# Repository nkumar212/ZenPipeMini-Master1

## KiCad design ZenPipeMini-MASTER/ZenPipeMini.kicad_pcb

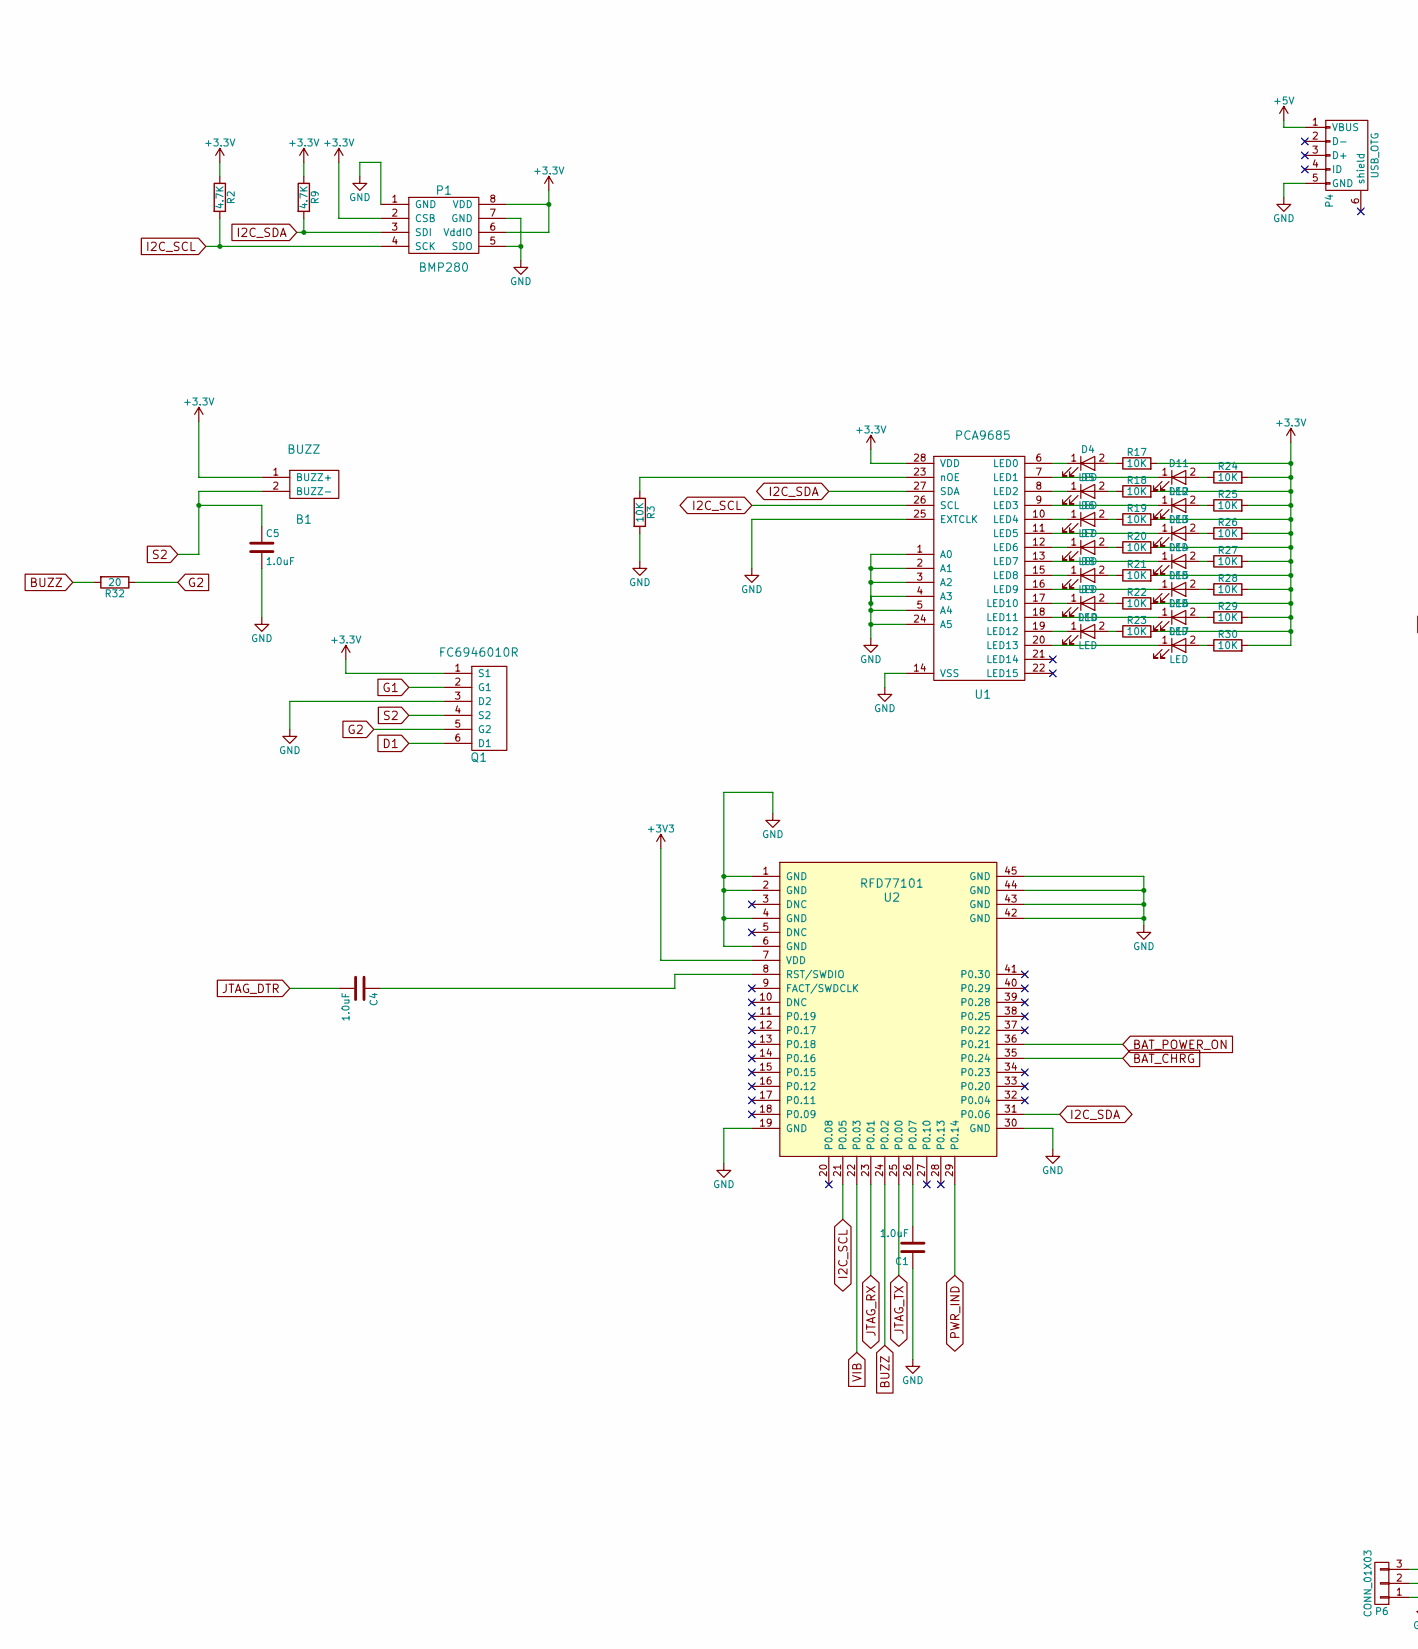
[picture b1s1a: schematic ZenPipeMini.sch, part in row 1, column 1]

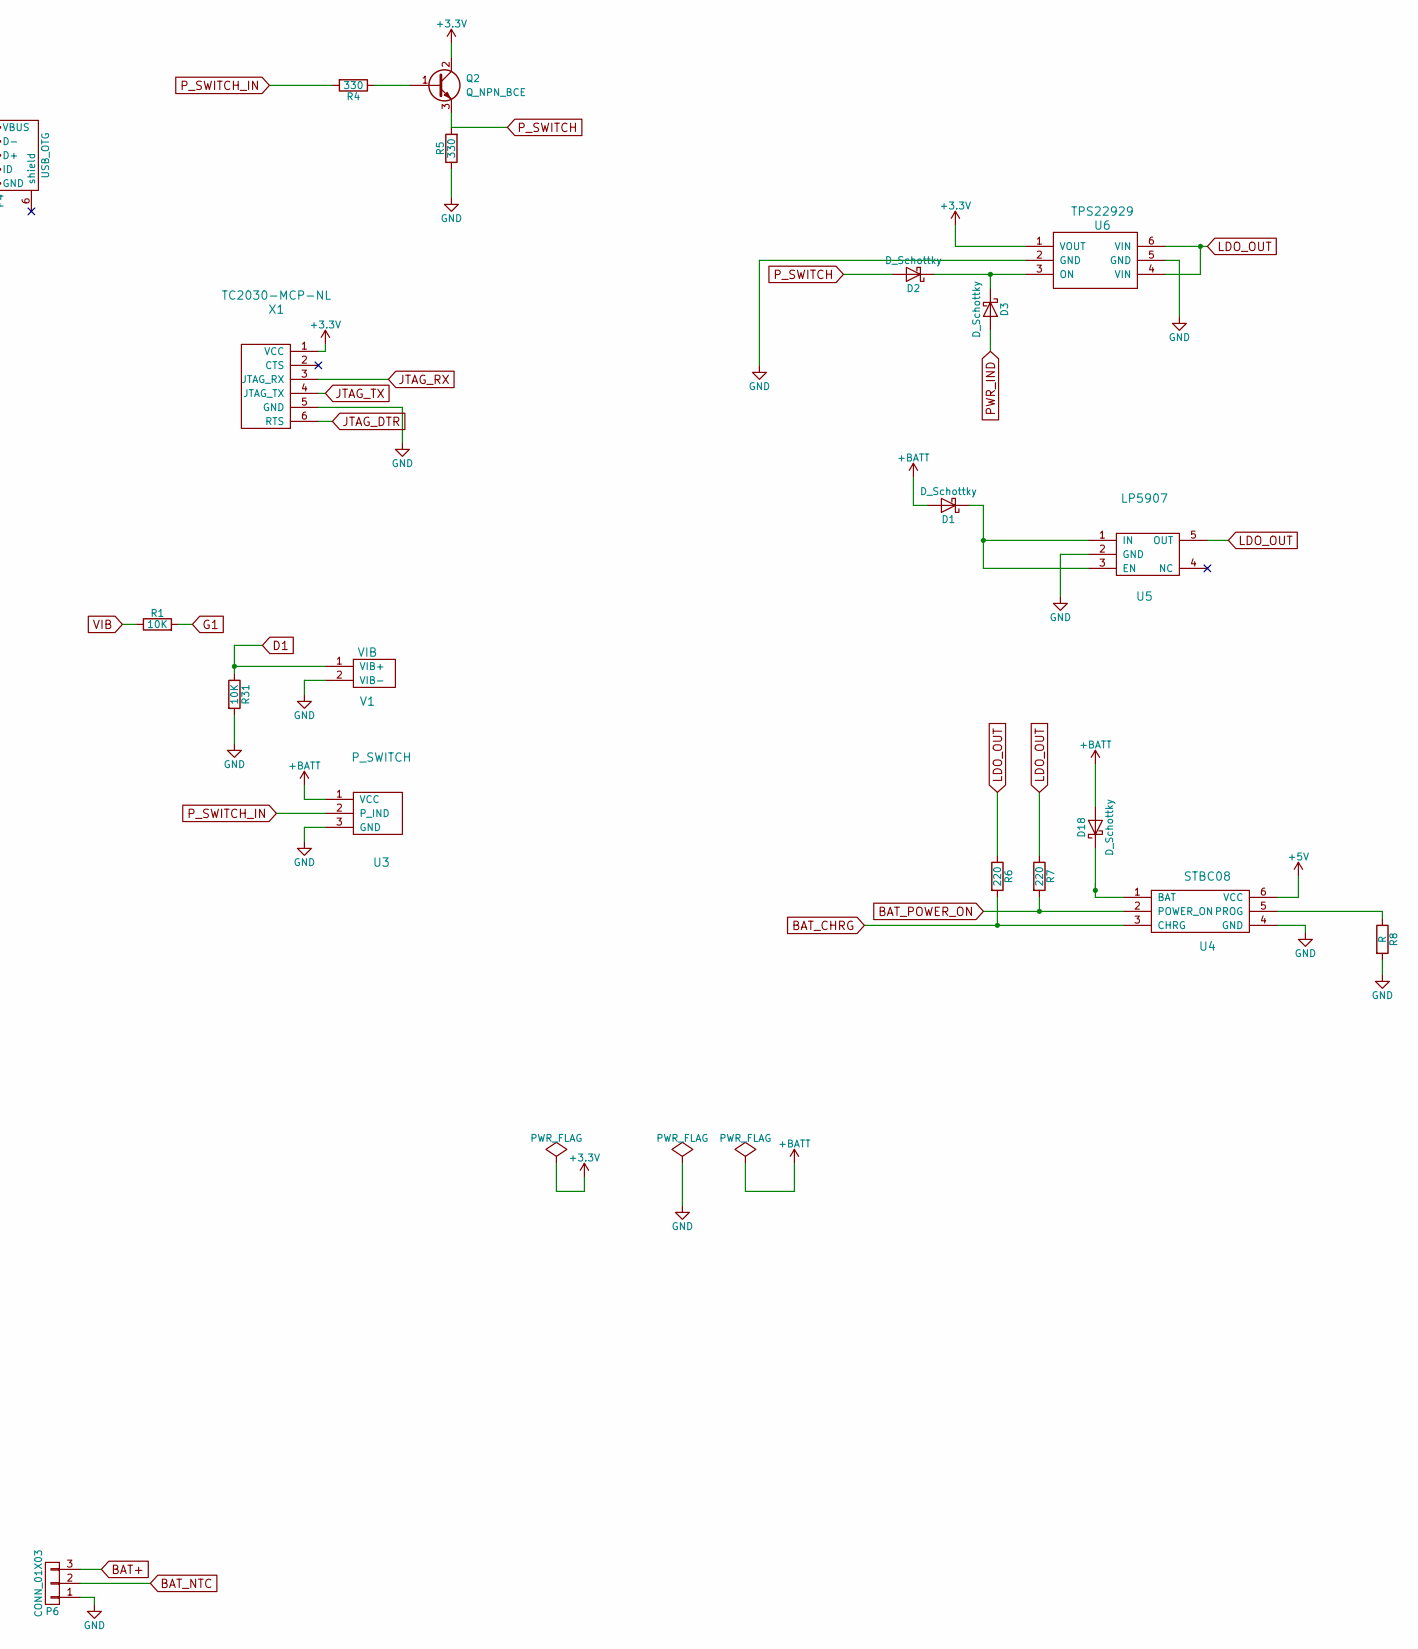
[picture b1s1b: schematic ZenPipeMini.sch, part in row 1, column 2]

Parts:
B1: BUZZ
C1, C4, C5: 1.0uF; C_0201
D1, D2, D3, D18: D_Schottky; D_0603
D4, D5, D6, D7, D8, D9, D10, D11, D12, D13, D14, D15, D16, D17: LED; LED_0402
P1: BMP280
P4: USB_OTG; USB_Micro-B
P6: CONN_01X03; BAT
Q1: FC6946010R
Q2: Q_NPN_BCE; SOT-23
R1, R3, R17, R18, R19, R20, R21, R22, R23, R24, R25, R26, R27, R28, R29, R30, R31: 10K; R_0201
R2, R9: 4.7K; R_0201
R4, R5: 330; R_0201
R6, R7: 220; R_0201
R8: R; R_0201
R32: 20; R_0201
U1: PCA9685; PCA9685_QFN
U2: RFD77101
U3: P_SWITCH
U4: STBC08
U5: LP5907
U6: TPS22929
V1: VIB
X1: TC2030-MCP-NL

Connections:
+5V: P4.1 (VBUS), U4.6 (VCC)
+BATT: D1.2 (A), D18.2 (A), U3.1 (VCC)
BAT+: P6.3
BAT_CHRG: R6.2, U2.35 (P0.24), U4.3 (CHRG)
BAT_NTC: P6.2
BAT_POWER_ON: R7.2, U2.36 (P0.21), U4.2 (POWER_ON)
BUZZ: R32.2, U2.24 (P0.02)
D1: Q1.6 (D1), R31.1, V1.1 (VIB+)
G1: Q1.2 (G1), R1.2
G2: Q1.5 (G2), R32.1
GND: C1.1, C5.2, P1.1 (GND), P1.5 (SDO), P1.7 (GND), P4.5 (GND), P6.1, Q1.3 (D2), R3.2, R5.1, R8.2, R31.2, U1.1 (A0), U1.2 (A1), U1.3 (A2), U1.4 (A3), U1.5 (A4), U1.14 (VSS), U1.24 (A5), U1.25 (EXTCLK), U2.1 (GND), U2.2 (GND), U2.4 (GND), U2.6 (GND), U2.19 (GND), U2.30 (GND), U2.42 (GND), U2.43 (GND), U2.44 (GND), U2.45 (GND), U3.3 (GND), U4.4 (GND), U5.2 (GND), U6.2 (GND), U6.5 (GND), V1.2 (VIB-), X1.5 (GND)
I2C_SCL: P1.4 (SCK), R2.2, U1.26 (SCL), U2.21 (P0.05)
I2C_SDA: P1.3 (SDI), R9.2, U1.27 (SDA), U2.31 (P0.06)
JTAG_DTR: C4.2, X1.6 (RTS)
JTAG_RX: U2.23 (P0.01), X1.3 (JTAG_RX)
JTAG_TX: U2.25 (P0.00), X1.4 (JTAG_TX)
LDO_OUT: R6.1, R7.1, U5.5 (OUT), U6.4 (VIN), U6.6 (VIN)
unnamed: C1.2, U2.26 (P0.07)
unnamed: C4.1, U2.8 (RST/SWDIO)
unnamed: D1.1 (K), U5.1 (IN), U5.3 (EN)
unnamed: D2.1 (K), D3.1 (K), U6.3 (ON)
unnamed: D4.1 (K), U1.6 (LED0)
unnamed: D4.2 (A), R17.1
unnamed: D5.1 (K), U1.8 (LED2)
unnamed: D5.2 (A), R18.1
unnamed: D6.1 (K), U1.10 (LED4)
unnamed: D6.2 (A), R19.1
unnamed: D7.1 (K), U1.12 (LED6)
unnamed: D7.2 (A), R20.1
unnamed: D8.1 (K), U1.15 (LED8)
unnamed: D8.2 (A), R21.1
unnamed: D9.1 (K), U1.17 (LED10)
unnamed: D9.2 (A), R22.1
unnamed: D10.1 (K), U1.19 (LED12)
unnamed: D10.2 (A), R23.1
unnamed: D11.1 (K), U1.7 (LED1)
unnamed: D11.2 (A), R24.1
unnamed: D12.1 (K), U1.9 (LED3)
unnamed: D12.2 (A), R25.1
unnamed: D13.1 (K), U1.11 (LED5)
unnamed: D13.2 (A), R26.1
unnamed: D14.1 (K), U1.13 (LED7)
unnamed: D14.2 (A), R27.1
unnamed: D15.1 (K), U1.16 (LED9)
unnamed: D15.2 (A), R28.1
unnamed: D16.1 (K), U1.18 (LED11)
unnamed: D16.2 (A), R29.1
unnamed: D17.1 (K), U1.20 (LED13)
unnamed: D17.2 (A), R30.1
unnamed: D18.1 (K), U4.1 (BAT)
unnamed: Q2.1 (B), R4.1
unnamed: R3.1, U1.23 (nOE)
unnamed: R8.1, U4.5 (PROG)
PWR_IND: D3.2 (A), U2.29 (P0.14)
P_SWITCH: D2.2 (A), Q2.3 (E), R5.2
P_SWITCH_IN: R4.2, U3.2 (P_IND)
S2: B1.2 (BUZZ-), C5.1, Q1.4 (S2)
VIB: R1.1, U2.22 (P0.03)

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
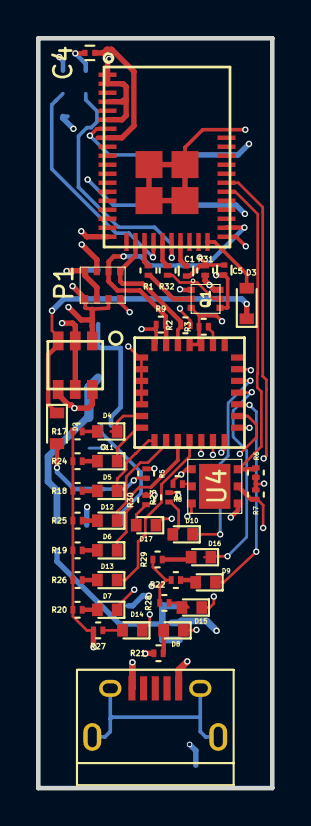
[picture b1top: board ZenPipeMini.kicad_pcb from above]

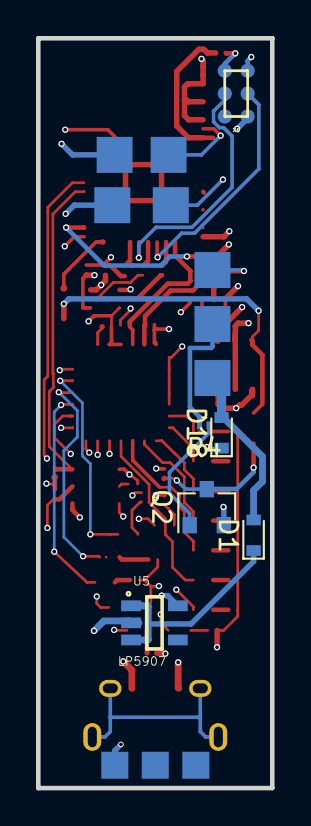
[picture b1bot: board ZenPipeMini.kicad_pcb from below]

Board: 4 copper layers, 13.0 x 41.7 mm, 60 parts (10 on the bottom side), 57 nets.

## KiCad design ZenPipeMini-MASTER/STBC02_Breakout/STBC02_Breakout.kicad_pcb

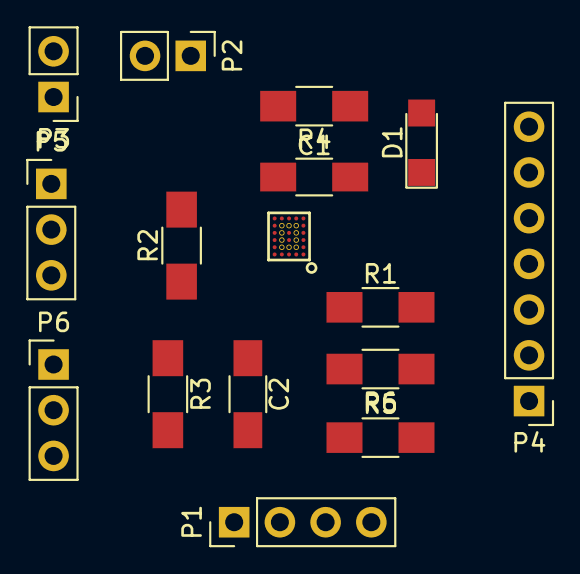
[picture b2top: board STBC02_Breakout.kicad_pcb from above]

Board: 2 copper layers, 16 parts (0 on the bottom side), 25 nets, no tracks yet.

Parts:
C1, C2: C; C_1206_HandSoldering
D1: LED; LED_1206
P1: CONN_01X04; Pin_Header_Straight_1x04_Pitch2.54mm
P2, P3: CONN_01X02; Pin_Header_Straight_1x02_Pitch2.54mm
P4: CONN_01X07; Pin_Header_Straight_1x07_Pitch2.54mm
P5, P6: CONN_01X03; Pin_Header_Straight_1x03_Pitch2.54mm
R1, R2, R3, R4, R5, R6: R; R_1206_HandSoldering
U1: STBC02

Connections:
+5V: U1.E5, U1.F5
BAT+: C2.1, P1.1, R3.1, U1.A5, U1.B3, U1.B5
BATMS: P1.2, R5.1, R6.2
BAT_NTC: P1.3, U1.D1
CEN: P4.2, U1.B1
GND: C2.2, P1.4, P2.2, P3.2, R1.2, R2.2, R6.1, U1.A3, U1.B4
LDO: C1.1, P2.1, R4.2, U1.F4
unnamed: D1.2, R4.1
unnamed: R1.1, U1.A4
unnamed: R2.1, U1.D4
unnamed: R3.2, U1.A2
unnamed: R5.2, U1.C4
RESET_NOW: P4.3, U1.A1
RST_PENDING: P4.4, U1.B2
SW1_I: P6.1, U1.F3
SW1_OA: P6.2, U1.E4
SW1_OB: P6.3, U1.E3
SW2_I: P5.1, U1.E2
SW2_OA: P5.2, U1.F2
SW2_OB: P5.3, U1.F1
SW_SEL: P4.6, U1.C1
SYS: P3.1, U1.C5, U1.D5
WAKE_UP: P4.7, U1.D2
nCHG: C1.2, D1.1, P4.1, U1.E1
nRESET: P4.5, U1.C2

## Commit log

2017-07-07 :boom::camel: Added .gitattributes & .gitignore files
2017-07-07 init
